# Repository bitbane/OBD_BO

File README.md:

# OBD_BO
OBD-II breakout board to screw terminals or pin headers.

You put an OBD-II connector at one end. You put screw terminals or pin headers at the other end. The big fat trace going to pin 16 is for power so make sure that the OBD-II connector pin 16 is oriented correctly. Most OBD-II connectors means that the OBD-II connector goes on the bottom of the PCB.

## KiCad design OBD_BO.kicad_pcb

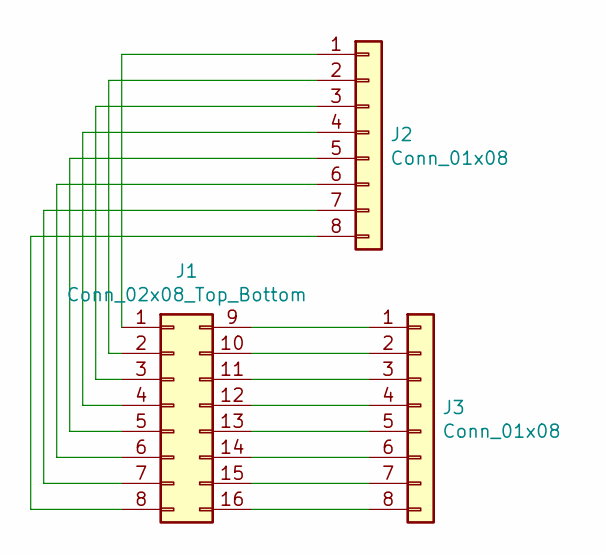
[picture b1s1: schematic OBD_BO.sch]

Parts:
J1: Conn_02x08_Top_Bottom; OBD-II
J2, J3: Conn_01x08; PinHeader_1x08_P2.54mm_Vertical

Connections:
unnamed: J1.1, J2.1
unnamed: J1.2, J2.2
unnamed: J1.3, J2.3
unnamed: J1.4, J2.4
unnamed: J1.5, J2.5
unnamed: J1.6, J2.6
unnamed: J1.7, J2.7
unnamed: J1.8, J2.8
unnamed: J1.9, J3.1
unnamed: J1.10, J3.2
unnamed: J1.11, J3.3
unnamed: J1.12, J3.4
unnamed: J1.13, J3.5
unnamed: J1.14, J3.6
unnamed: J1.15, J3.7
unnamed: J1.16, J3.8

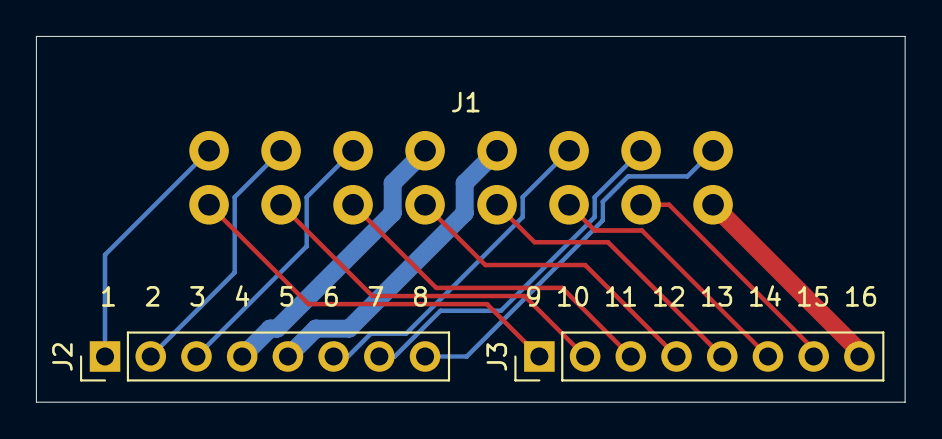
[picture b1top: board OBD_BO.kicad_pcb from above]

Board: 2 copper layers, 48.3 x 20.3 mm, 3 parts (0 on the bottom side), 16 nets.

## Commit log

2021-08-17 Silly little OBD-II breakout to screw terminals (or pin headers, I'm not picky)
2021-08-17 Committed my gerber directory instead of the kicad directory... whoops. Fixing that
